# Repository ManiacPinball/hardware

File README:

I will add a real README later. But for now some points:

You can use this for your personal non commercial use.

Currently the Com device used for the arduino is still hardcoded, therefore you have to adjust it before compiling the dll. Just open the Led.cpp and change COM10 in line 20 to your needs.

In the arduino folder you will find the code which needs to be uploaded to your Arduino.

In the eagle folder youl find the schematics and board layouts in eagle format.

The pinjoy firmware is still missing, I'm trying currently to get the USB descriptor right for the 3 analog axis.

The ledcontrol.vbs is a slightly modified version to use the usbled dll. I will update this file soon with the new version appeared recently.

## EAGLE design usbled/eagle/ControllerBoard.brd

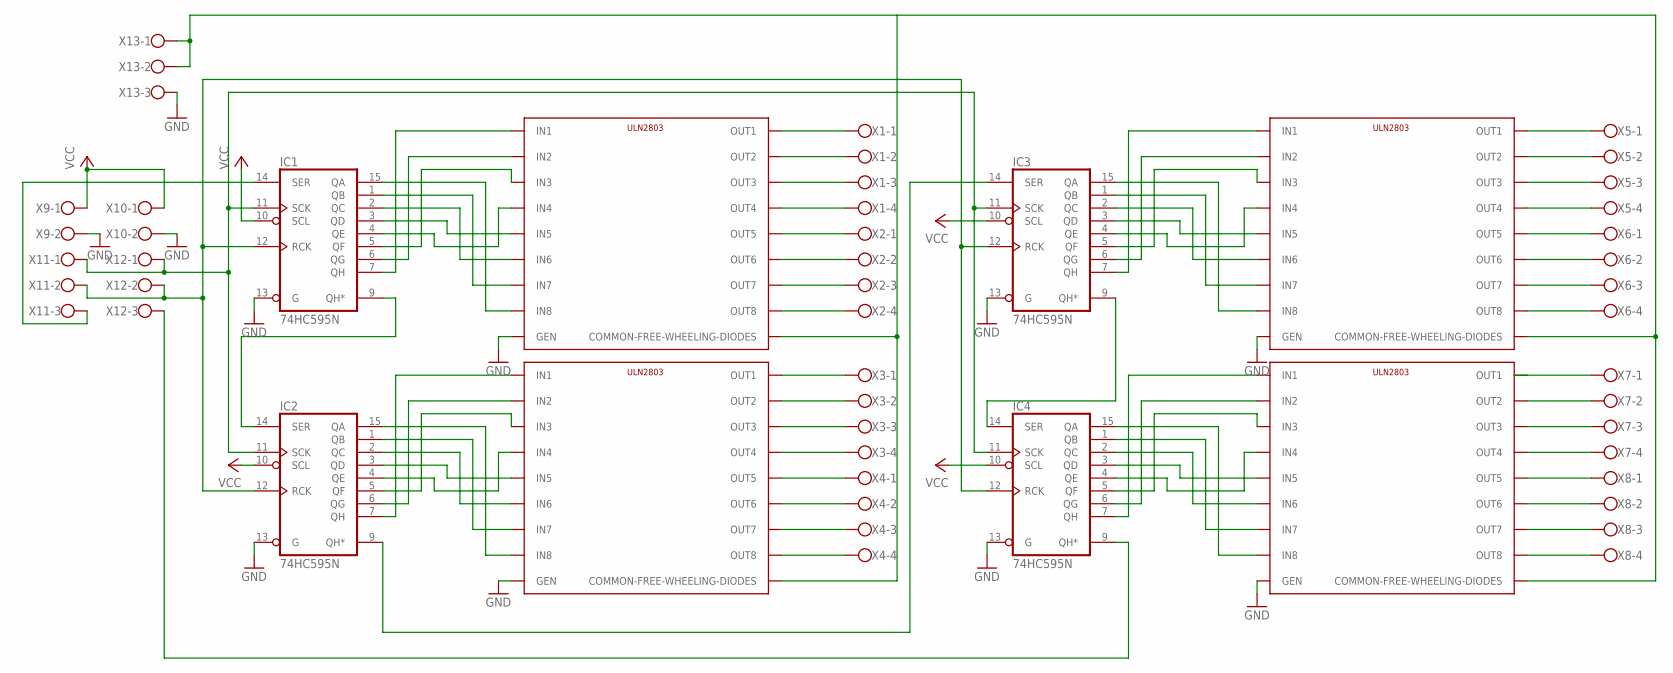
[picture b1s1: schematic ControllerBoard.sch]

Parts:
IC1, IC2, IC3, IC4: 74HC595N; DIL16
U$1, U$2, U$3, U$4: ULN2803; P-DIP
X1, X2, X3, X4, X5, X6, X7, X8: W237-4
X9, X10: W237-102
X11, X12, X13: W237-103

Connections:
GND: IC1.8 (GND), IC1.13 (G), IC2.8 (GND), IC2.13 (G), IC3.8 (GND), IC3.13 (G), IC4.8 (GND), IC4.13 (G), U$1.GEN, U$2.GEN, U$3.GEN, U$4.GEN, X9.2, X10.2, X13.3
unnamed: IC1.9 (QH*), IC2.14 (SER)
unnamed: IC2.7 (QH), U$3.IN1
unnamed: IC1.15 (QA), U$1.IN8
unnamed: IC1.1 (QB), U$1.IN7
unnamed: IC1.2 (QC), U$1.IN6
unnamed: IC1.3 (QD), U$1.IN5
unnamed: IC1.4 (QE), U$1.IN4
unnamed: IC1.5 (QF), U$1.IN3
unnamed: IC1.6 (QG), U$1.IN2
unnamed: IC1.7 (QH), U$1.IN1
unnamed: IC2.6 (QG), U$3.IN2
unnamed: IC2.5 (QF), U$3.IN3
unnamed: IC2.15 (QA), U$3.IN8
unnamed: IC2.1 (QB), U$3.IN7
unnamed: IC2.2 (QC), U$3.IN6
unnamed: IC2.4 (QE), U$3.IN4
unnamed: IC2.3 (QD), U$3.IN5
unnamed: IC1.14 (SER), X11.3
unnamed: U$1.OUT1, X1.1
unnamed: U$1.OUT2, X1.2
unnamed: U$1.OUT3, X1.3
unnamed: U$1.OUT4, X1.4
unnamed: U$1.OUT5, X2.1
unnamed: U$1.OUT6, X2.2
unnamed: U$1.OUT7, X2.3
unnamed: U$1.OUT8, X2.4
unnamed: U$3.OUT1, X3.1
unnamed: U$3.OUT2, X3.2
unnamed: U$3.OUT3, X3.3
unnamed: U$3.OUT4, X3.4
unnamed: U$3.OUT5, X4.1
unnamed: U$3.OUT6, X4.2
unnamed: U$3.OUT7, X4.3
unnamed: U$3.OUT8, X4.4
unnamed: IC3.7 (QH), U$2.IN1
unnamed: IC3.6 (QG), U$2.IN2
unnamed: IC3.5 (QF), U$2.IN3
unnamed: IC3.4 (QE), U$2.IN4
unnamed: IC3.3 (QD), U$2.IN5
unnamed: IC3.2 (QC), U$2.IN6
unnamed: IC3.1 (QB), U$2.IN7
unnamed: IC3.15 (QA), U$2.IN8
unnamed: U$4.OUT1, X7.1
unnamed: U$2.OUT1, X5.1
unnamed: U$2.OUT2, X5.2
unnamed: U$2.OUT3, X5.3
unnamed: U$2.OUT4, X5.4
unnamed: U$2.OUT5, X6.1
unnamed: U$2.OUT6, X6.2
unnamed: U$2.OUT7, X6.3
unnamed: IC4.7 (QH), U$4.IN1
unnamed: IC4.6 (QG), U$4.IN2
unnamed: IC4.5 (QF), U$4.IN3
unnamed: IC4.4 (QE), U$4.IN4
unnamed: IC4.3 (QD), U$4.IN5
unnamed: IC4.2 (QC), U$4.IN6
unnamed: IC4.1 (QB), U$4.IN7
unnamed: IC4.15 (QA), U$4.IN8
unnamed: U$2.OUT8, X6.4
unnamed: U$4.OUT2, X7.2
unnamed: U$4.OUT3, X7.3
unnamed: U$4.OUT4, X7.4
unnamed: U$4.OUT5, X8.1
unnamed: U$4.OUT6, X8.2
unnamed: U$4.OUT7, X8.3
unnamed: U$4.OUT8, X8.4
unnamed: IC2.9 (QH*), IC3.14 (SER)
unnamed: IC3.9 (QH*), IC4.14 (SER)
unnamed: U$1.COMMON-FREE-WHEELIN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, U$2.COMMON-FREE-WHEELIN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, U$3.COMMON-FREE-WHEELIN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, U$4.COMMON-FREE-WHEELIN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, X13.1, X13.2
unnamed: IC4.9 (QH*), X12.3
unnamed: IC1.11 (SCK), IC2.11 (SCK), IC3.11 (SCK), IC4.11 (SCK), X11.1, X12.1
unnamed: IC1.12 (RCK), IC2.12 (RCK), IC3.12 (RCK), IC4.12 (RCK), X11.2, X12.2
VCC: IC1.10 (SCL), IC1.16 (VCC), IC2.10 (SCL), IC2.16 (VCC), IC3.10 (SCL), IC3.16 (VCC), IC4.10 (SCL), IC4.16 (VCC), X9.1, X10.1

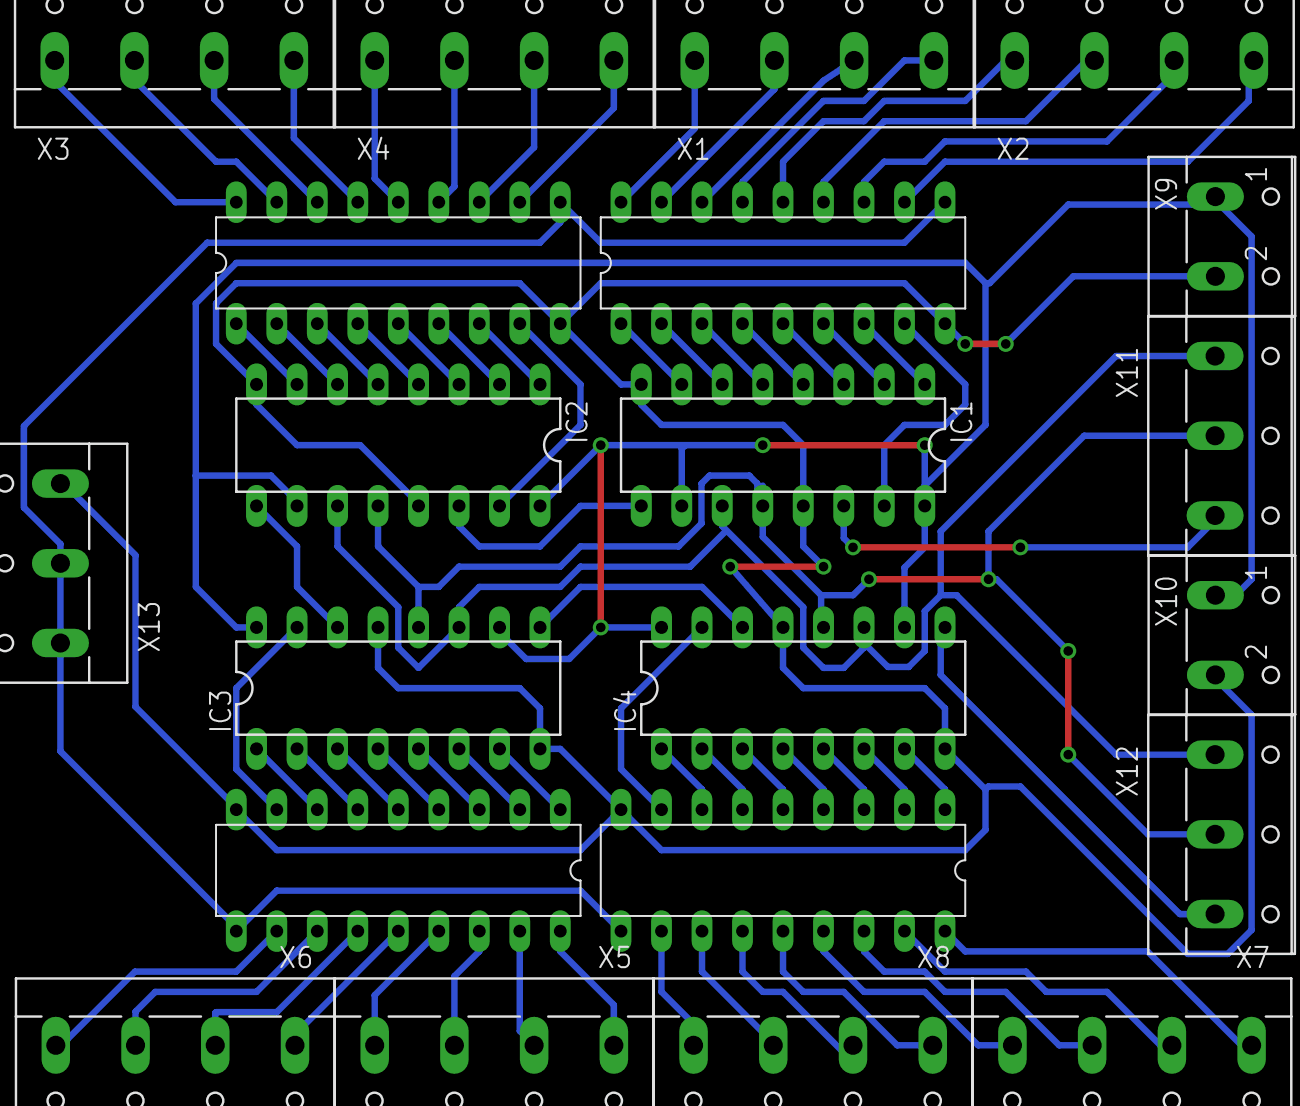
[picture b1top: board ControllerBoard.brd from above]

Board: 2 copper layers, 21 parts (0 on the bottom side), 74 nets.

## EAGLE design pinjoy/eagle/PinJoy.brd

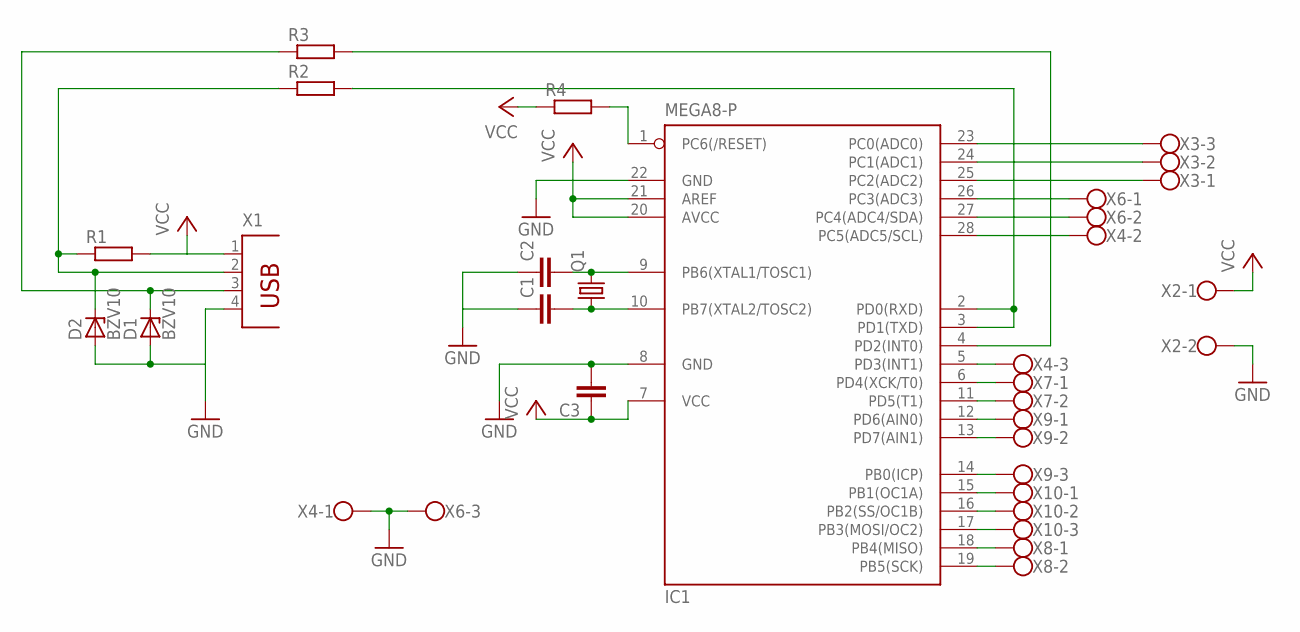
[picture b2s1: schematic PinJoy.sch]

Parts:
C1, C2, C3: C-EU025-024X044; C025-024X044
D1, D2: BZV10; DO34Z7
IC1: MEGA8-P; DIL28-3
Q1: CRYSTALHC18U-V; HC18U-V
R1, R2, R3, R4: R-EU_0204/7; 0204/7
X1: PN61729
X2, X7, X8: W237-102
X3, X4, X6, X9, X10: W237-103

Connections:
GND: C1.1, C2.1, C3.2, D1.A, D2.A, IC1.8 (GND), IC1.22 (GND), X1.4, X2.2, X4.1, X6.3
unnamed: C2.2, IC1.9 (PB6(XTAL1/TOSC1)), Q1.2
unnamed: C1.2, IC1.10 (PB7(XTAL2/TOSC2)), Q1.1
unnamed: IC1.19 (PB5(SCK)), X8.2
unnamed: D2.C, R1.1, R2.1, X1.2
unnamed: IC1.2 (PD0(RXD)), IC1.3 (PD1(TXD)), R2.2
unnamed: IC1.4 (PD2(INT0)), R3.2
unnamed: D1.C, R3.1, X1.3
unnamed: IC1.18 (PB4(MISO)), X8.1
unnamed: IC1.17 (PB3(MOSI/OC2)), X10.3
unnamed: IC1.25 (PC2(ADC2)), X3.1
unnamed: IC1.16 (PB2(SS/OC1B)), X10.2
unnamed: IC1.15 (PB1(OC1A)), X10.1
unnamed: IC1.24 (PC1(ADC1)), X3.2
unnamed: IC1.23 (PC0(ADC0)), X3.3
unnamed: IC1.26 (PC3(ADC3)), X6.1
unnamed: IC1.27 (PC4(ADC4/SDA)), X6.2
unnamed: IC1.13 (PD7(AIN1)), X9.2
unnamed: IC1.12 (PD6(AIN0)), X9.1
unnamed: IC1.11 (PD5(T1)), X7.2
unnamed: IC1.6 (PD4(XCK/T0)), X7.1
unnamed: IC1.5 (PD3(INT1)), X4.3
unnamed: IC1.28 (PC5(ADC5/SCL)), X4.2
unnamed: IC1.14 (PB0(ICP)), X9.3
unnamed: IC1.1 (PC6(/RESET)), R4.2
VCC: C3.1, IC1.7 (VCC), IC1.20 (AVCC), IC1.21 (AREF), R1.2, R4.1, X1.1, X2.1

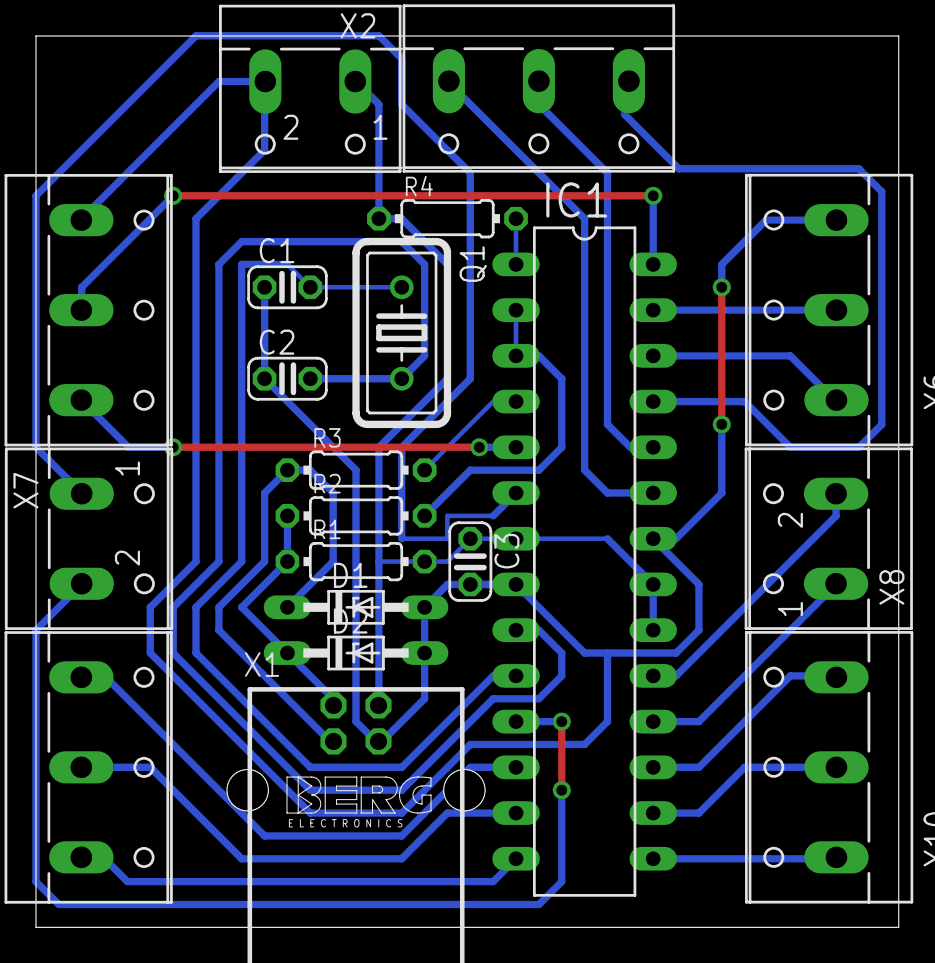
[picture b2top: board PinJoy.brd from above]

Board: 2 copper layers, 47.9 x 49.5 mm, 20 parts (0 on the bottom side), 26 nets.

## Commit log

2013-03-04 initial import
2013-03-04 changed COM name from Test2 to the new one
2013-03-04 add small READNE
2013-03-26 add PWM to the arduino firmware
